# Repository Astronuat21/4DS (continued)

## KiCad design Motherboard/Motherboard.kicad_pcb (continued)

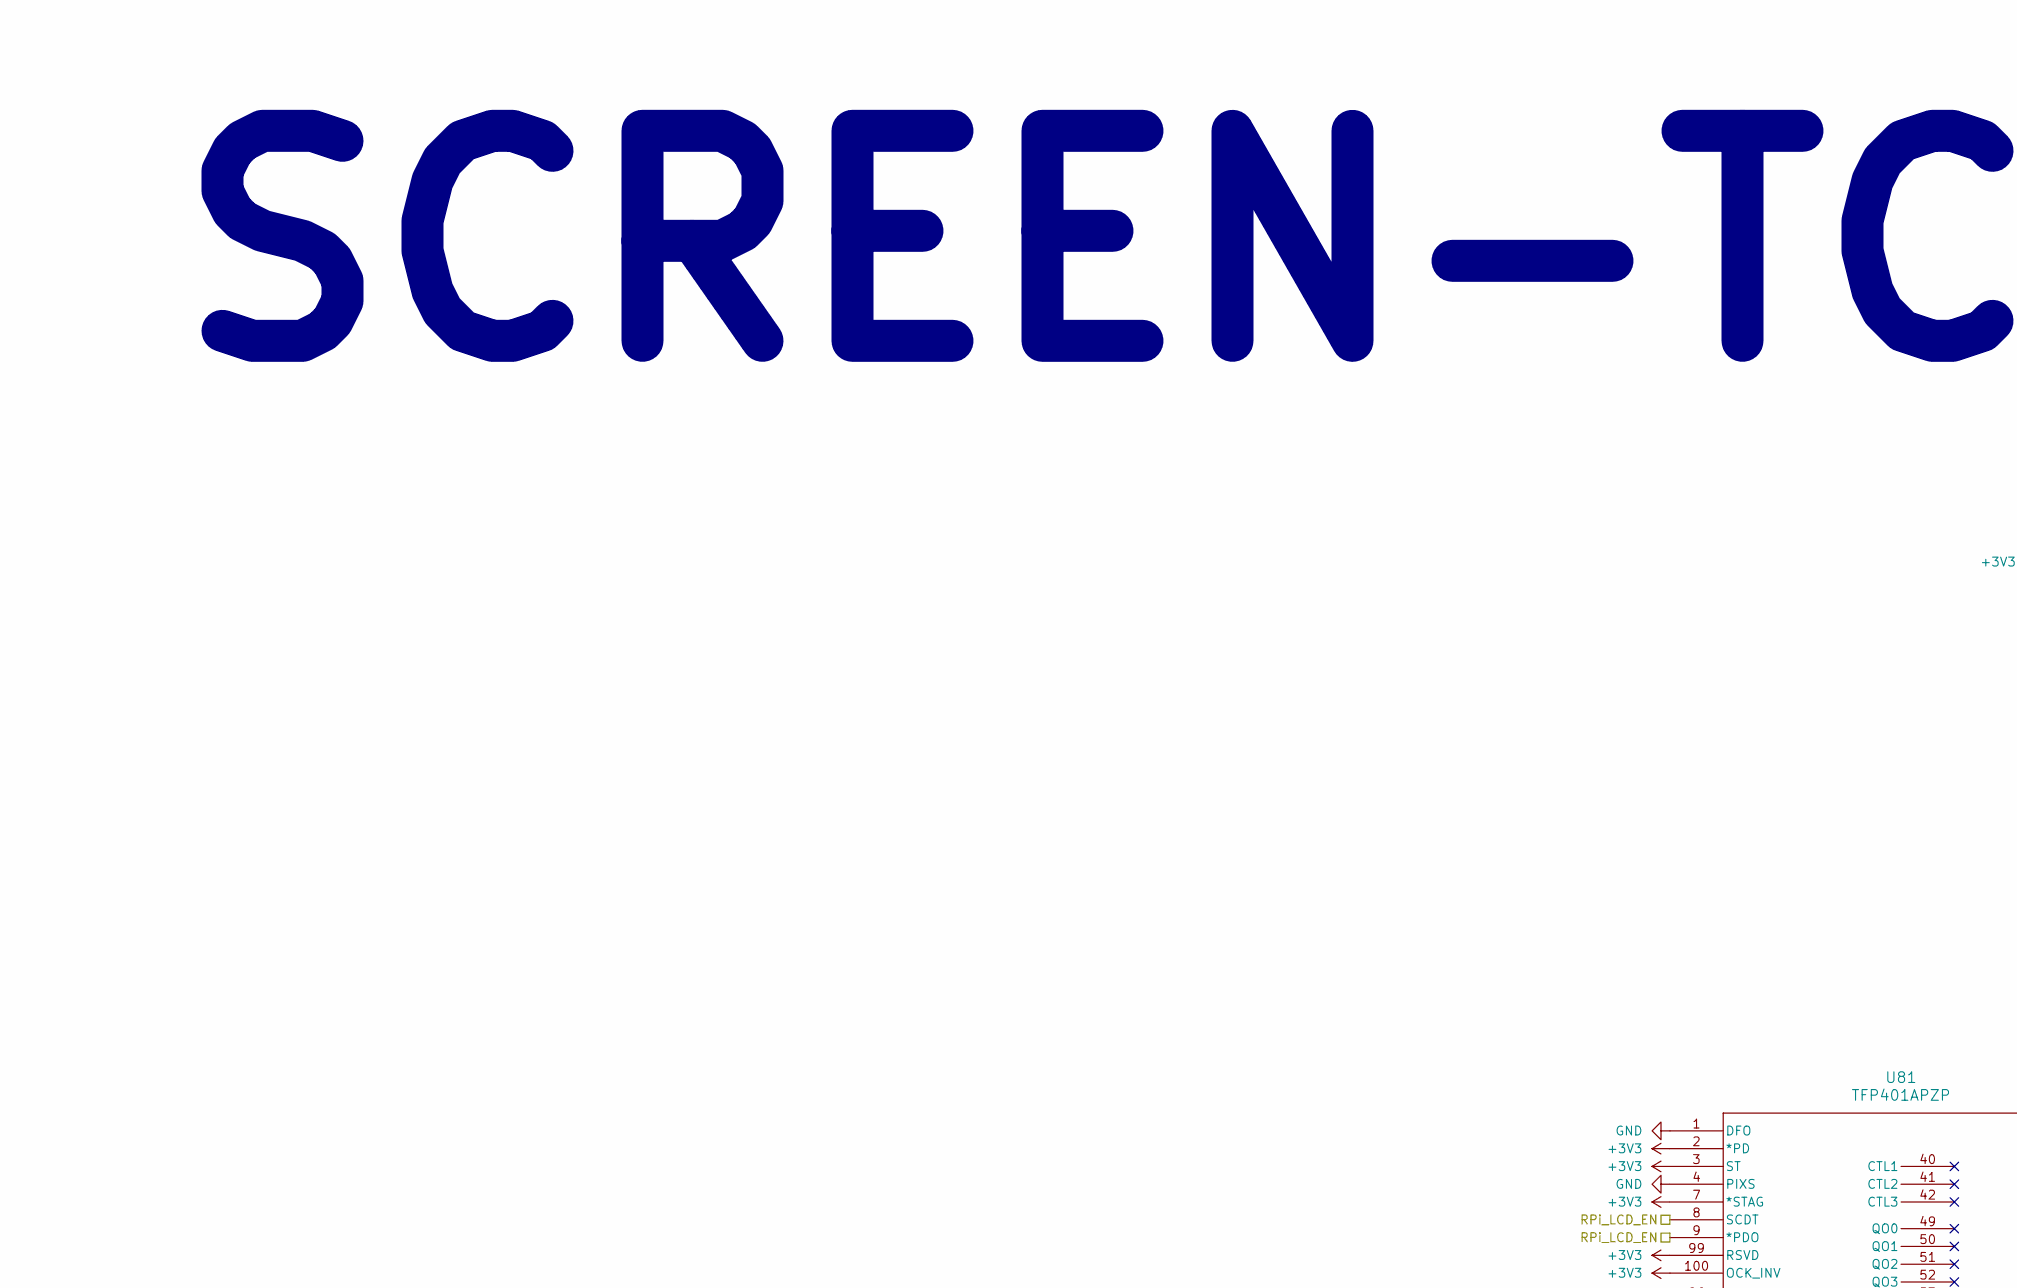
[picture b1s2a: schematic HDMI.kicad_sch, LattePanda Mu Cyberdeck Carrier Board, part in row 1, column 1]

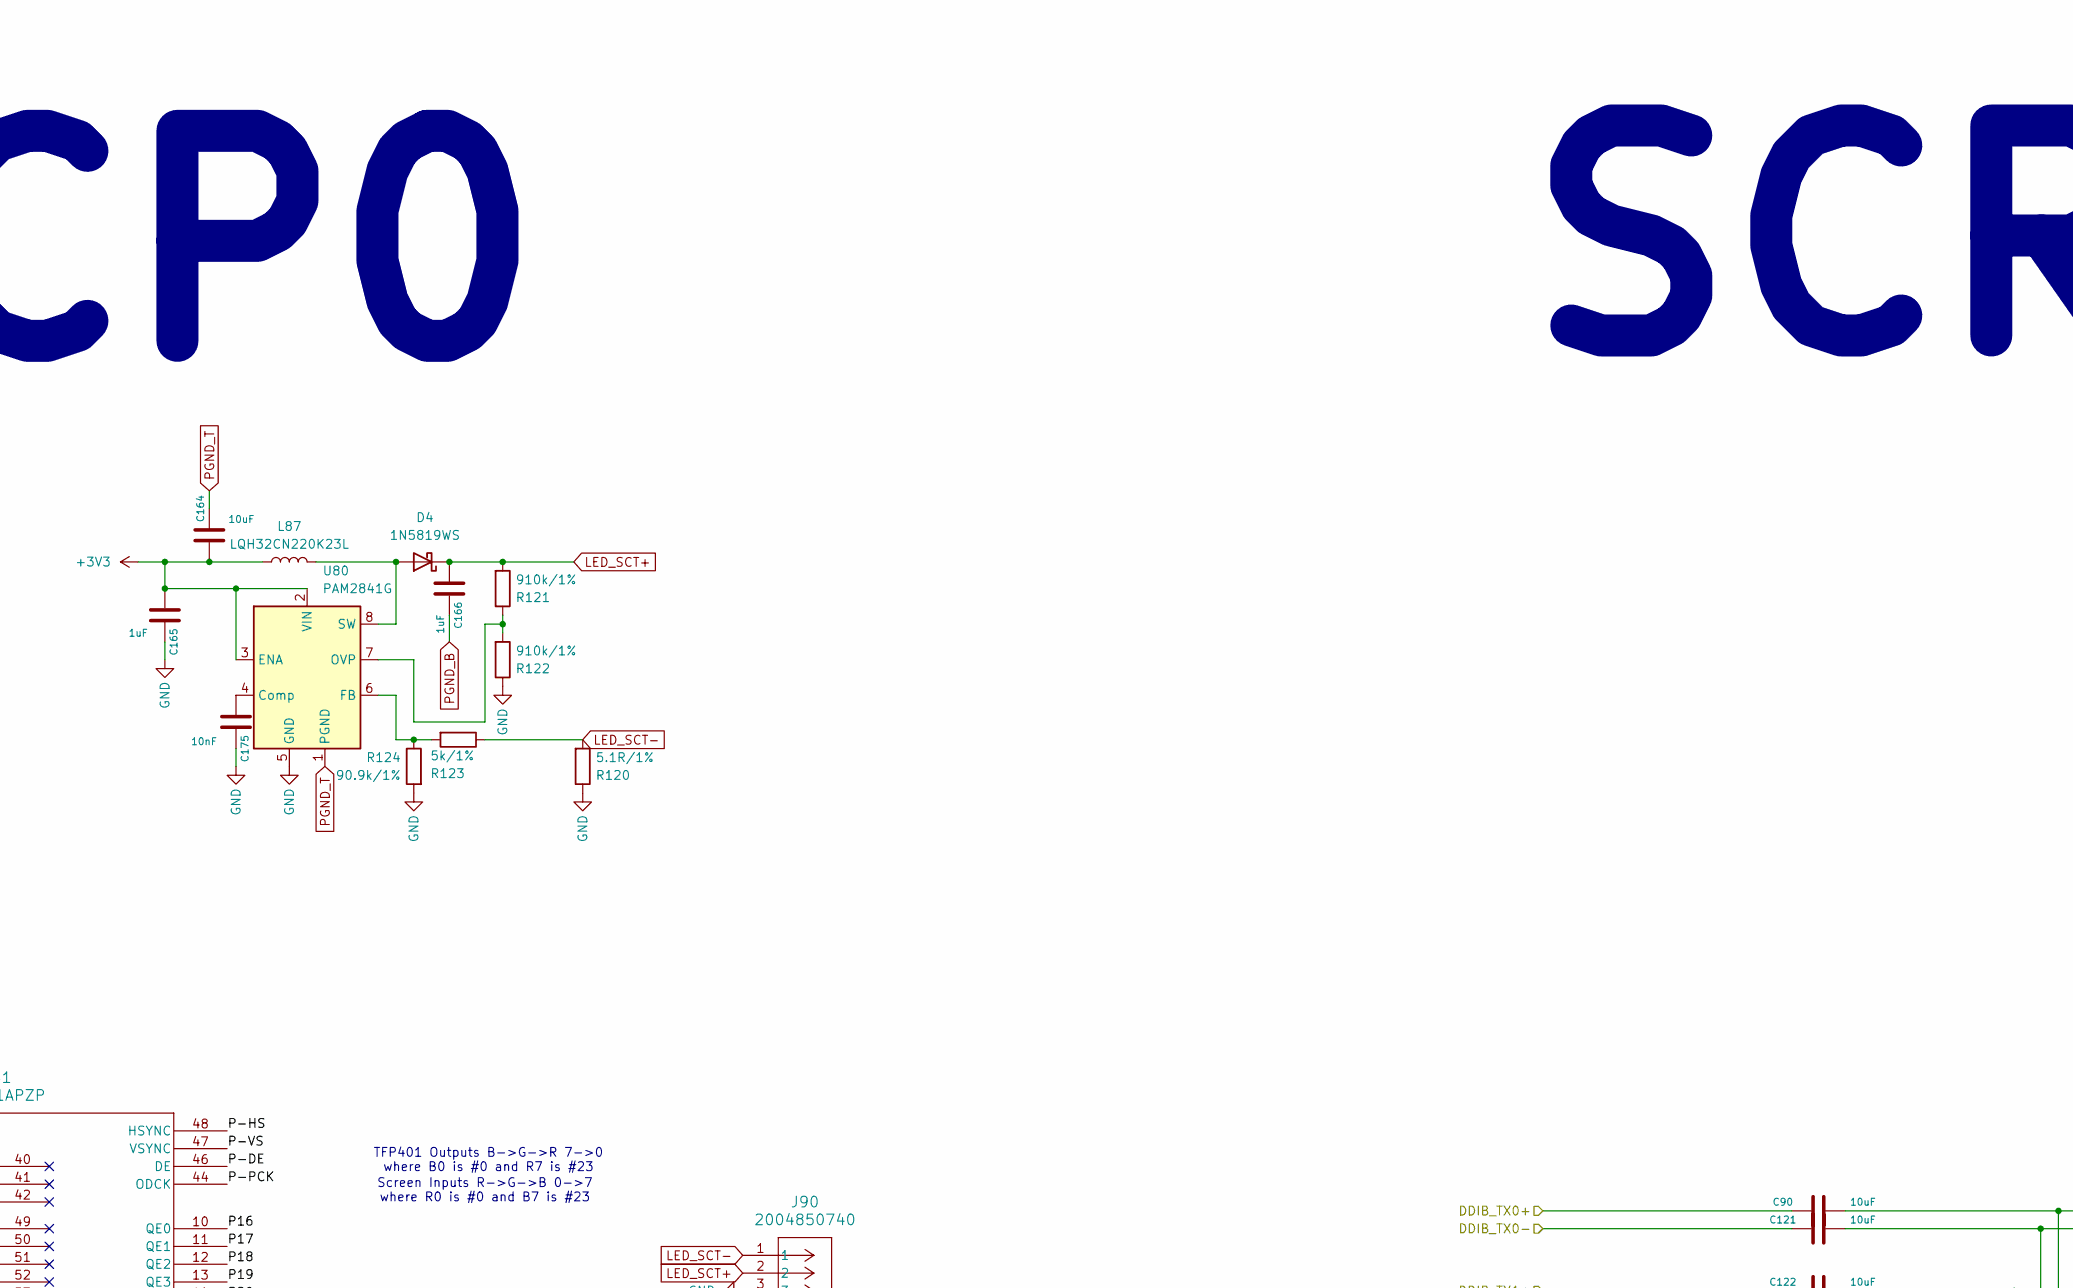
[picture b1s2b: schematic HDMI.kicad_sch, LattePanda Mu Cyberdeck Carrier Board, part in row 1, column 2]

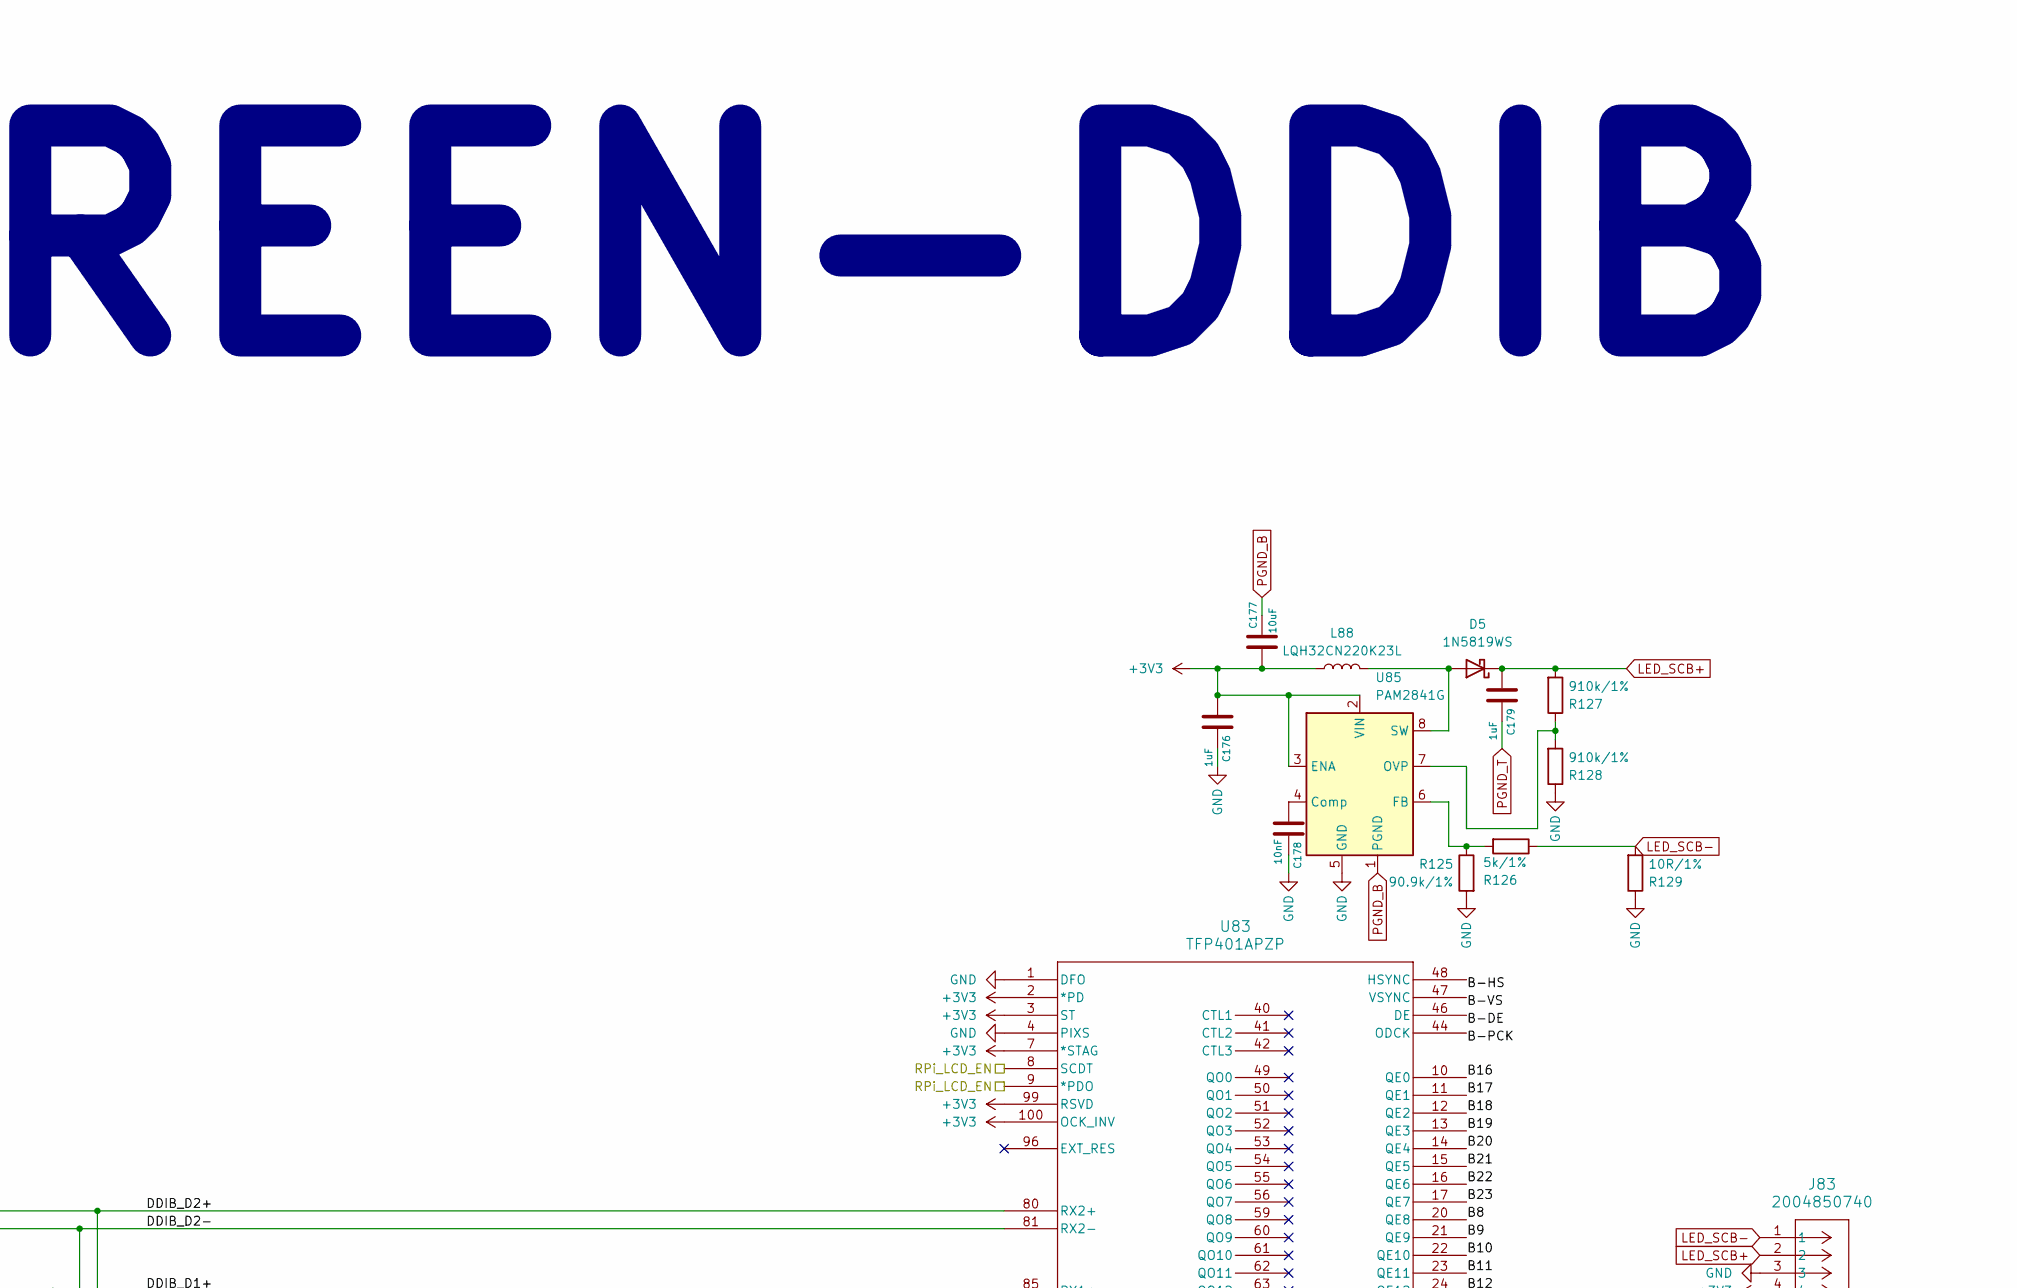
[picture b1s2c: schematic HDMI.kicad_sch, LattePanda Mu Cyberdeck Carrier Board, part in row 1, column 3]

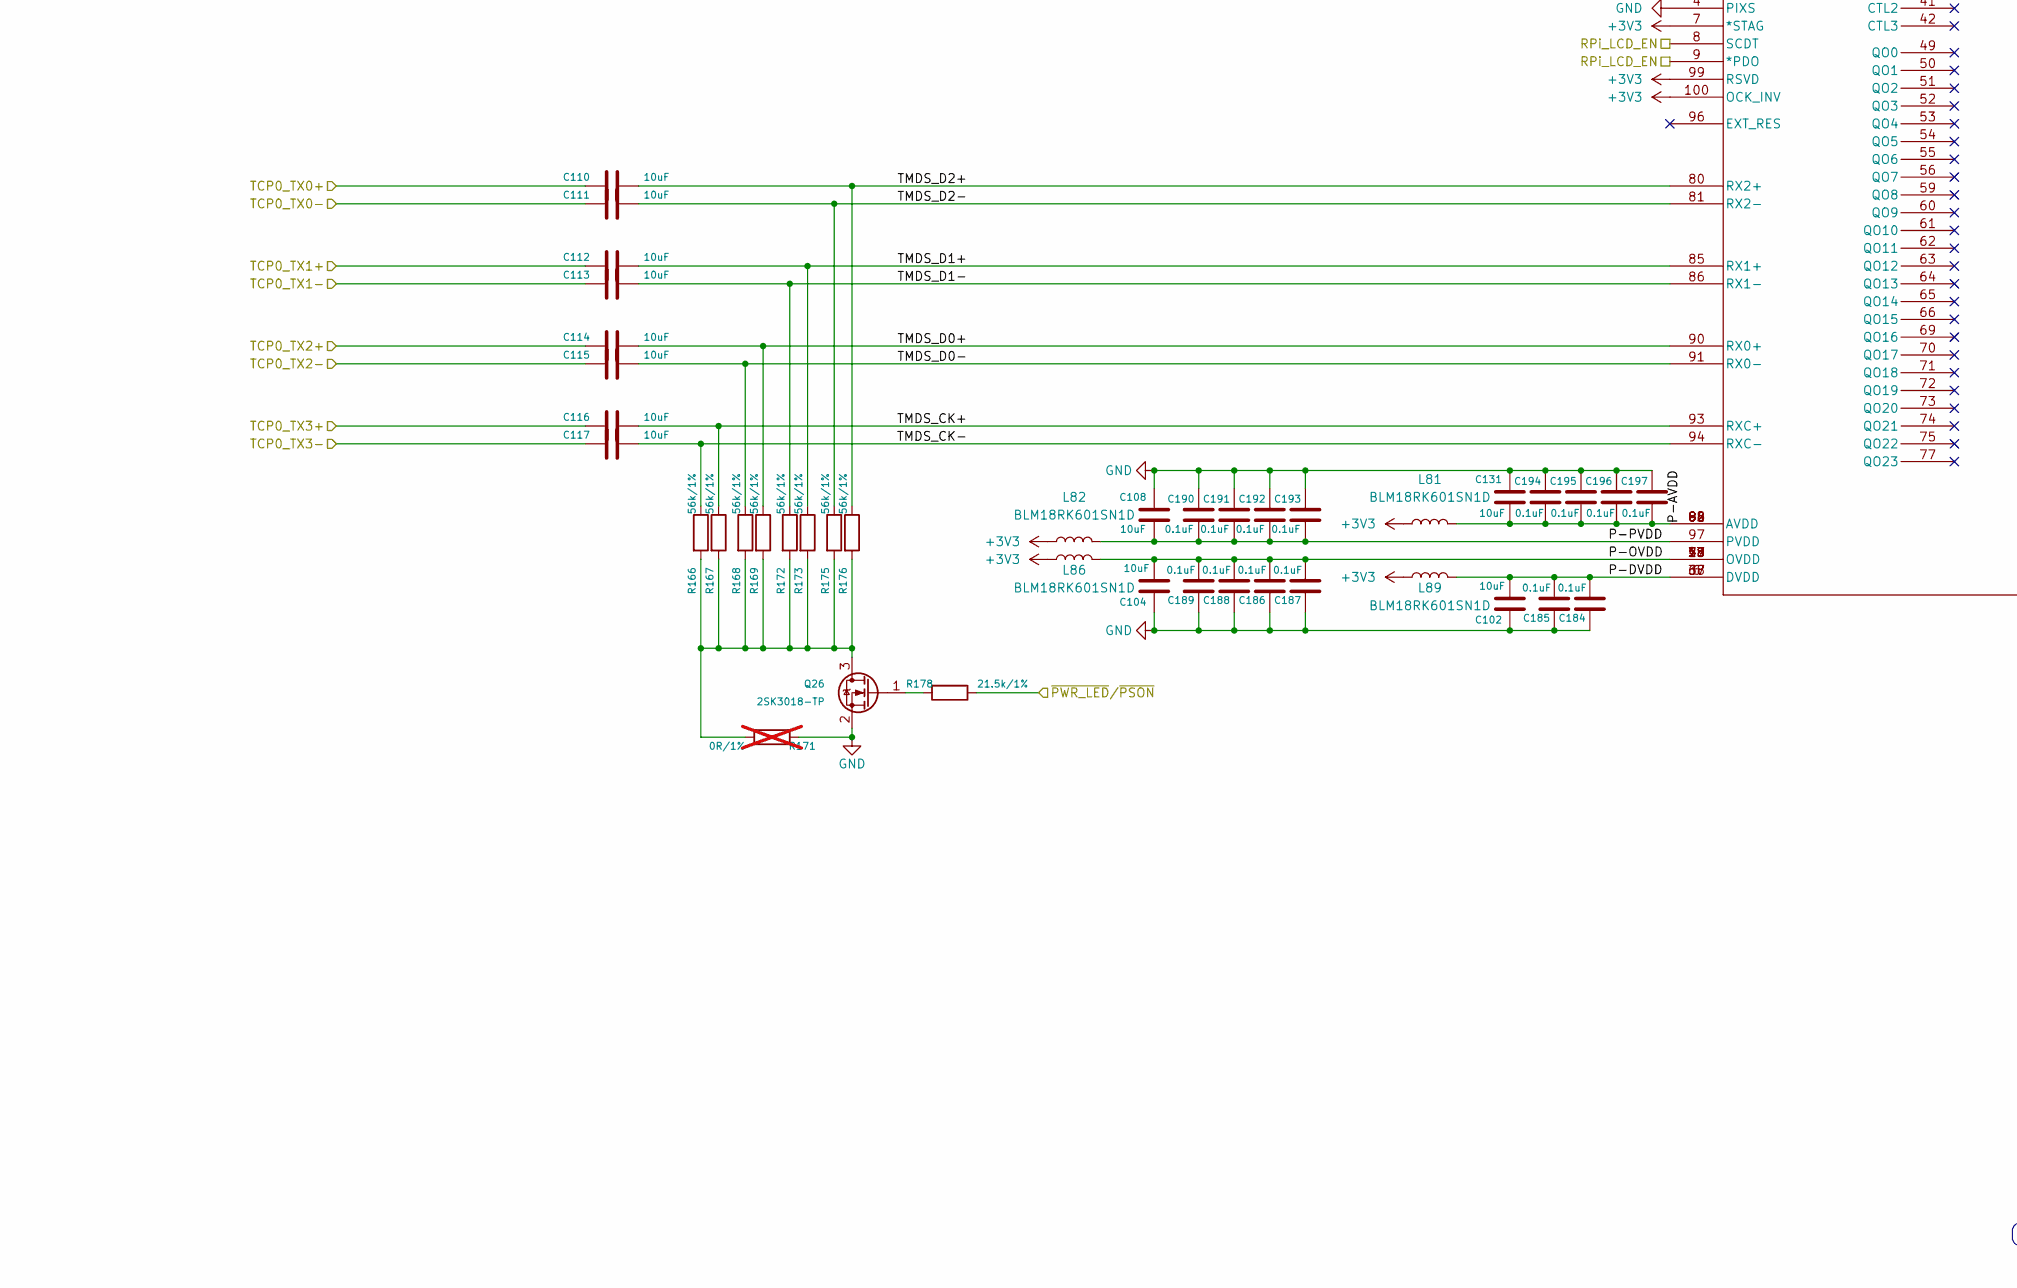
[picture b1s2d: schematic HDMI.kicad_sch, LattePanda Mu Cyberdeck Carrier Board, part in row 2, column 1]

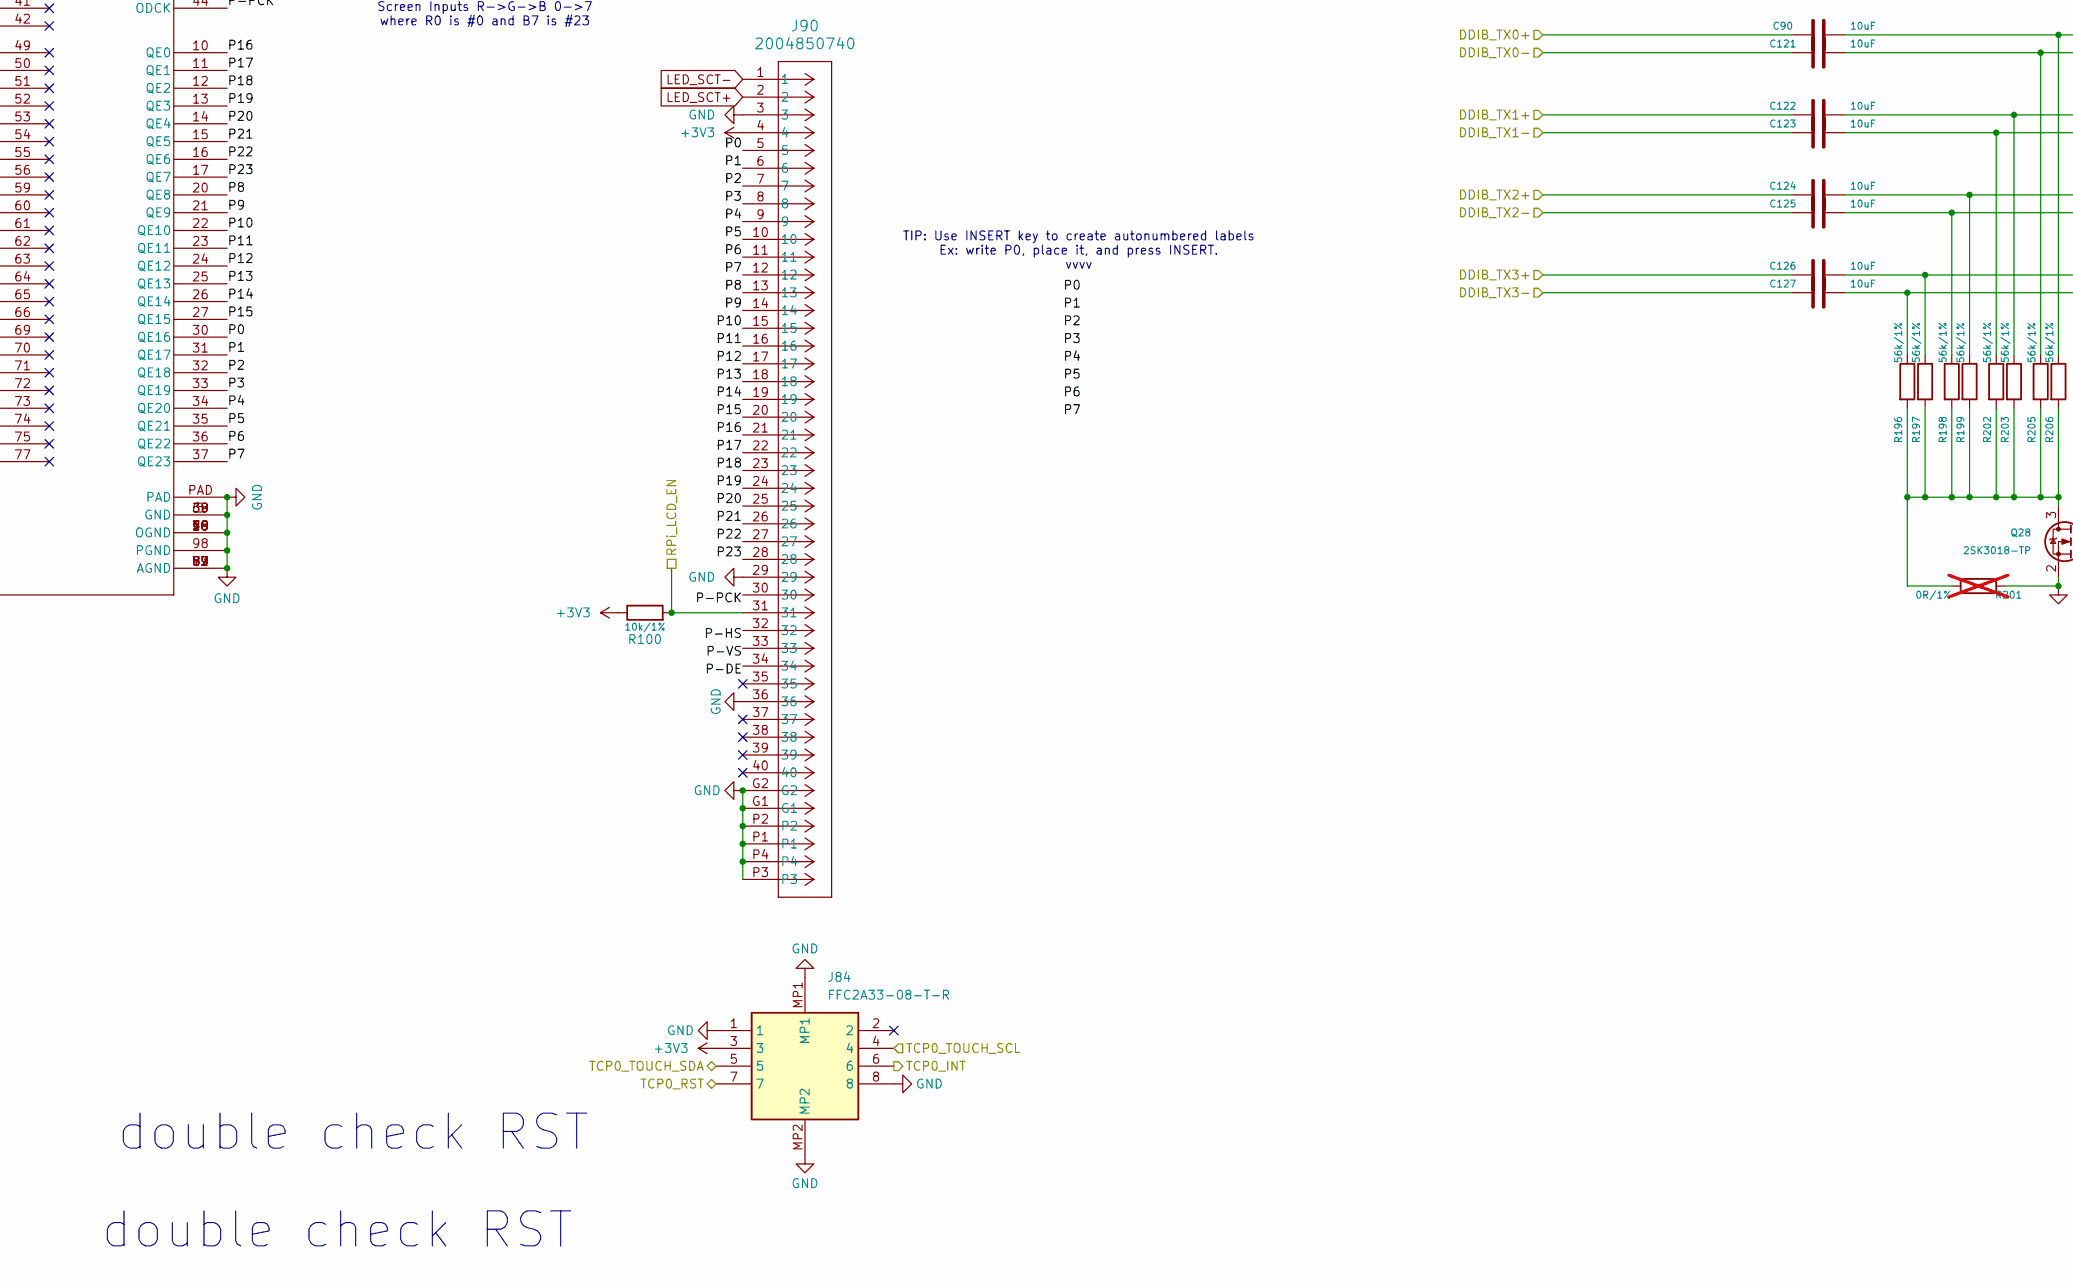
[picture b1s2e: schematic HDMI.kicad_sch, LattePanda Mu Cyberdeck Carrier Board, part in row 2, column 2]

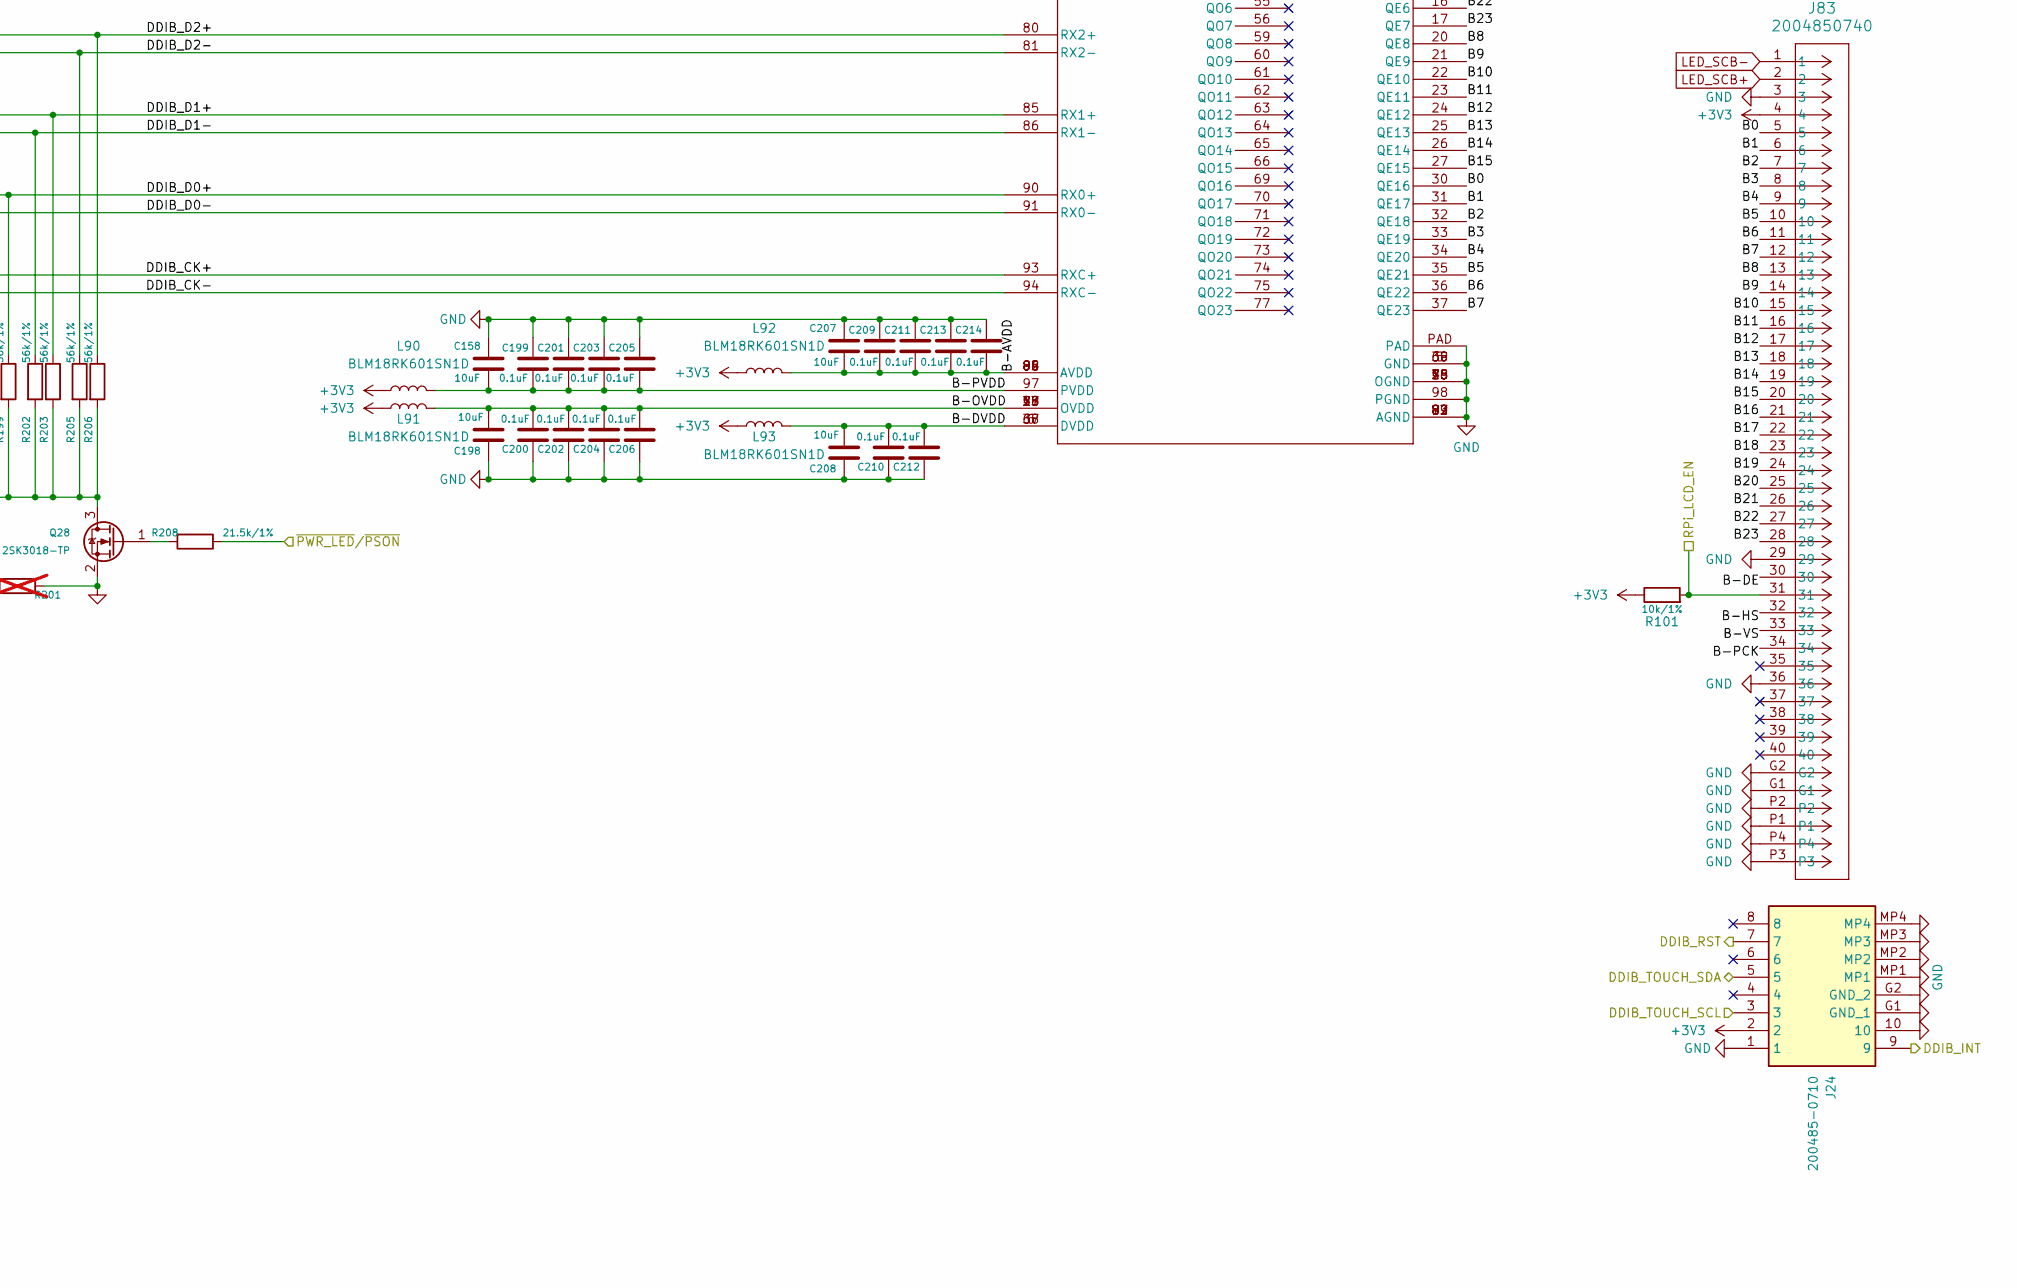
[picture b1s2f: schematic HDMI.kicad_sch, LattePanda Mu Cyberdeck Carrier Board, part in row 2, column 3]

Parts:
C90, C102, C104, C108, C110, C111, C112, C113, C114, C115, C116, C117, C121, C122, C123, C124, C125, C126, C127, C131, C164, C177, C207, C208: 10uF; C_0402_1005Metric; MPN GMC04X5R106M10NT
C158, C198: 10uF; C_0402_1005Metric; MPN GRM155R60J106ME15D
C165, C166, C176, C179: 1uF; C_0402_1005Metric; MPN TCC0402X5R105M100AT
C175, C178: 10nF; C_0402_1005Metric; MPN GRM155R61C103KA01D
C184, C185, C186, C187, C188, C189, C190, C191, C192, C193, C194, C195, C196, C197, C199, C200, C201, C202, C203, C204, C205, C206, C209, C210, C211, C212, C213, C214: 0.1uF; C_0402_1005Metric; MPN any/open
D4, D5: 1N5819WS; D_SOD-323; MPN 1N5819WS
J24: 200485-0710; 2004850710; MPN 2004850710
J83, J90: 2004850740; CON_2004850740; MPN 2004850740
J84: FFC2A33-08-T-R; FFC2A3308TR; MPN FFC2A33-08-T-R
L81, L82, L86, L89, L90, L91, L92, L93: BLM18RK601SN1D; L_0603_1608Metric; MPN BLM18RK601SN1D
L87, L88: LQH32CN220K23L; LQH32DN100K23L; MPN LQH32CN220K23L
Q26, Q28: 2SK3018-TP; SOT-89-3; MPN 2SK3018-TP
R100, R101: 10k/1%; R_0402_1005Metric; MPN MCR01MZPF1002
R120: 5.1R/1%; R_0402_1005Metric; MPN AC0402FR-075R1L
R121, R122, R127, R128: 910k/1%; R_0402_1005Metric; MPN 0402WGF9103TCE
R123, R126: 5k/1%; R_0402_1005Metric; MPN RC0402FR-075KL
R124, R125: 90.9k/1%; R_0805_2012Metric; MPN any/open
R129: 10R/1%; R_0402_1005Metric; MPN CRG0402F10R
R166, R167, R168, R169, R172, R173, R175, R176, R196, R197, R198, R199, R202, R203, R205, R206: 56k/1%; R_0402_1005Metric; MPN CRGCQ0402F56K
R171, R201: 0R/1%; R_0402_1005Metric; not fitted
R178, R208: 21.5k/1%; R_0402_1005Metric; MPN 0402WGF2152TCE
U80, U85: PAM2841G; DFN-8-1EP_2x2mm_P0.5mm_EP0.86x1.55mm; MPN PAM2841GR
U81, U83: TFP401APZP; PZP100_5P2X5P2; MPN TFP401APZP

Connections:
+3V3: C164.2, C165.2, C176.2, C177.2, J24.2, J83.4, J84.3, J90.4, L81.1, L82.1, L86.1, L87.1, L87.3, L88.1, L88.3, L89.1, L90.1, L91.1, L92.1, L93.1, R100.1, R101.1, U80.2 (VIN), U80.3 (ENA), U81.2 (*PD), U81.3 (ST), U81.7 (*STAG), U81.99 (RSVD), U81.100 (OCK_INV), U83.2 (*PD), U83.3 (ST), U83.7 (*STAG), U83.99 (RSVD), U83.100 (OCK_INV), U85.2 (VIN), U85.3 (ENA); also elsewhere on the board
/LattePanda Module/DDIB_INT: J24.9; also elsewhere on the board
/LattePanda Module/DDIB_RST: J24.7; also elsewhere on the board
/LattePanda Module/DDIB_TOUCH_SCL: J24.3; also elsewhere on the board
/LattePanda Module/DDIB_TOUCH_SDA: J24.5; also elsewhere on the board
/LattePanda Module/DDIB_TX0+: C90.1; also elsewhere on the board
/LattePanda Module/DDIB_TX0-: C121.1; also elsewhere on the board
/LattePanda Module/DDIB_TX1+: C122.1; also elsewhere on the board
/LattePanda Module/DDIB_TX1-: C123.1; also elsewhere on the board
/LattePanda Module/DDIB_TX2+: C124.1; also elsewhere on the board
/LattePanda Module/DDIB_TX2-: C125.1; also elsewhere on the board
/LattePanda Module/DDIB_TX3+: C126.1; also elsewhere on the board
/LattePanda Module/DDIB_TX3-: C127.1; also elsewhere on the board
/LattePanda Module/RPi_LCD_EN: J83.31, J90.31, R100.2, R101.2, U81.8 (SCDT), U81.9 (*PDO), U83.8 (SCDT), U83.9 (*PDO); also elsewhere on the board
/LattePanda Module/TCP0_INT: J84.6; also elsewhere on the board
/LattePanda Module/TCP0_RST: J84.7; also elsewhere on the board
/LattePanda Module/TCP0_TOUCH_SCL: J84.4; also elsewhere on the board
/LattePanda Module/TCP0_TOUCH_SDA: J84.5; also elsewhere on the board
/LattePanda Module/TCP0_TX0+: C110.1; also elsewhere on the board
/LattePanda Module/TCP0_TX0-: C111.1; also elsewhere on the board
/LattePanda Module/TCP0_TX1+: C112.1; also elsewhere on the board
/LattePanda Module/TCP0_TX1-: C113.1; also elsewhere on the board
/LattePanda Module/TCP0_TX2+: C114.1; also elsewhere on the board
/LattePanda Module/TCP0_TX2-: C115.1; also elsewhere on the board
/LattePanda Module/TCP0_TX3+: C116.1; also elsewhere on the board
/LattePanda Module/TCP0_TX3-: C117.1; also elsewhere on the board
/RGB/B0: J83.5, U83.30 (QE16)
/RGB/B1: J83.6, U83.31 (QE17)
/RGB/B2: J83.7, U83.32 (QE18)
/RGB/B3: J83.8, U83.33 (QE19)
/RGB/B4: J83.9, U83.34 (QE20)
/RGB/B5: J83.10, U83.35 (QE21)
/RGB/B6: J83.11, U83.36 (QE22)
/RGB/B7: J83.12, U83.37 (QE23)
/RGB/B8: J83.13, U83.20 (QE8)
/RGB/B9: J83.14, U83.21 (QE9)
/RGB/B10: J83.15, U83.22 (QE10)
/RGB/B11: J83.16, U83.23 (QE11)
/RGB/B12: J83.17, U83.24 (QE12)
/RGB/B13: J83.18, U83.25 (QE13)
/RGB/B14: J83.19, U83.26 (QE14)
/RGB/B15: J83.20, U83.27 (QE15)
/RGB/B16: J83.21, U83.10 (QE0)
/RGB/B17: J83.22, U83.11 (QE1)
/RGB/B18: J83.23, U83.12 (QE2)
/RGB/B19: J83.24, U83.13 (QE3)
/RGB/B20: J83.25, U83.14 (QE4)
/RGB/B21: J83.26, U83.15 (QE5)
/RGB/B22: J83.27, U83.16 (QE6)
/RGB/B23: J83.28, U83.17 (QE7)
/RGB/B-AVDD: C207.2, C209.1, C211.1, C213.1, C214.1, L92.2, U83.82 (AVDD), U83.84 (AVDD), U83.88 (AVDD), U83.95 (AVDD)
/RGB/B-DE: J83.30, U83.46 (DE)
/RGB/B-DVDD: C208.2, C210.1, C212.1, L93.2, U83.6 (DVDD), U83.38 (DVDD), U83.67 (DVDD)
/RGB/B-HS: J83.32, U83.48 (HSYNC)
/RGB/B-OVDD: C198.2, C200.1, C202.1, C204.1, C206.1, L91.2, U83.18 (OVDD), U83.29 (OVDD), U83.43 (OVDD), U83.57 (OVDD), U83.78 (OVDD)
/RGB/B-PCK: J83.34, U83.44 (ODCK)
/RGB/B-PVDD: C158.2, C199.1, C201.1, C203.1, C205.1, L90.2, U83.97 (PVDD)
/RGB/B-VS: J83.33, U83.47 (VSYNC)
/RGB/DDIB_CK+: C126.2, R197.1, U83.93 (RXC+)
/RGB/DDIB_CK-: C127.2, R196.1, U83.94 (RXC-)
/RGB/DDIB_D0+: C124.2, R199.1, U83.90 (RX0+)
/RGB/DDIB_D0-: C125.2, R198.1, U83.91 (RX0-)
/RGB/DDIB_D1+: C122.2, R203.1, U83.85 (RX1+)
/RGB/DDIB_D1-: C123.2, R202.1, U83.86 (RX1-)
/RGB/DDIB_D2+: C90.2, R206.1, U83.80 (RX2+)
/RGB/DDIB_D2-: C121.2, R205.1, U83.81 (RX2-)
/RGB/P0: J90.5, U81.30 (QE16)
/RGB/P1: J90.6, U81.31 (QE17)
/RGB/P2: J90.7, U81.32 (QE18)
/RGB/P3: J90.8, U81.33 (QE19)
/RGB/P4: J90.9, U81.34 (QE20)
/RGB/P5: J90.10, U81.35 (QE21)
/RGB/P6: J90.11, U81.36 (QE22)
/RGB/P7: J90.12, U81.37 (QE23)
/RGB/P8: J90.13, U81.20 (QE8)
/RGB/P9: J90.14, U81.21 (QE9)
/RGB/P10: J90.15, U81.22 (QE10)
/RGB/P11: J90.16, U81.23 (QE11)
/RGB/P12: J90.17, U81.24 (QE12)
/RGB/P13: J90.18, U81.25 (QE13)
/RGB/P14: J90.19, U81.26 (QE14)
/RGB/P15: J90.20, U81.27 (QE15)
/RGB/P16: J90.21, U81.10 (QE0)
/RGB/P17: J90.22, U81.11 (QE1)
/RGB/P18: J90.23, U81.12 (QE2)
/RGB/P19: J90.24, U81.13 (QE3)
/RGB/P20: J90.25, U81.14 (QE4)
/RGB/P21: J90.26, U81.15 (QE5)
/RGB/P22: J90.27, U81.16 (QE6)
/RGB/P23: J90.28, U81.17 (QE7)
/RGB/P-AVDD: C131.2, C194.1, C195.1, C196.1, C197.1, L81.2, U81.82 (AVDD), U81.84 (AVDD), U81.88 (AVDD), U81.95 (AVDD)
/RGB/P-DE: J90.34, U81.46 (DE)
/RGB/P-DVDD: C102.2, C184.1, C185.1, L89.2, U81.6 (DVDD), U81.38 (DVDD), U81.67 (DVDD)
/RGB/P-HS: J90.32, U81.48 (HSYNC)
/RGB/P-OVDD: C104.2, C186.1, C187.1, C188.1, C189.1, L86.2, U81.18 (OVDD), U81.29 (OVDD), U81.43 (OVDD), U81.57 (OVDD), U81.78 (OVDD)
/RGB/P-PCK: J90.30, U81.44 (ODCK)
/RGB/P-PVDD: C108.2, C190.1, C191.1, C192.1, C193.1, L82.2, U81.97 (PVDD)
/RGB/P-VS: J90.33, U81.47 (VSYNC)
/RGB/TMDS_CK+: C116.2, R167.1, U81.93 (RXC+)
/RGB/TMDS_CK-: C117.2, R166.1, U81.94 (RXC-)
/RGB/TMDS_D0+: C114.2, R169.1, U81.90 (RX0+)
/RGB/TMDS_D0-: C115.2, R168.1, U81.91 (RX0-)
/RGB/TMDS_D1+: C112.2, R173.1, U81.85 (RX1+)
/RGB/TMDS_D1-: C113.2, R172.1, U81.86 (RX1-)
/RGB/TMDS_D2+: C110.2, R176.1, U81.80 (RX2+)
/RGB/TMDS_D2-: C111.2, R175.1, U81.81 (RX2-)
/~PWR_LED/~PSON: R178.1, R208.1; also elsewhere on the board
GND: C102.1, C104.1, C108.1, C131.1, C158.1, C165.1, C175.1, C176.1, C178.1, C184.2, C185.2, C186.2, C187.2, C188.2, C189.2, C190.2, C191.2, C192.2, C193.2, C194.2, C195.2, C196.2, C197.2, C198.1, C199.2, C200.2, C201.2, C202.2, C203.2, C204.2, C205.2, C206.2, C207.1, C208.1, C209.2, C210.2, C211.2, C212.2, C213.2, C214.2, J24.1, J24.10, J24.G1 (GND_1), J24.G2 (GND_2), J24.MP1, J24.MP2, J24.MP3, J24.MP4, J83.3, J83.29, J83.36, J83.G1, J83.G2, J83.P1, J83.P2, J83.P3, J83.P4, J84.1, J84.8, J84.MP1, J84.MP2, J90.3, J90.29, J90.36, J90.G1, J90.G2, J90.P1, J90.P2, J90.P3, J90.P4, Q26.2 (S), Q28.2 (S), R120.1, R122.1, R124.2, R125.2, R128.1, R129.1, R171.2, R201.2, U80.5 (GND), U80.9 (GND), U81.1 (DFO), U81.4 (PIXS), U81.5 (GND), U81.19 (OGND), U81.28 (OGND), U81.39 (GND), U81.45 (OGND), U81.58 (OGND), U81.68 (GND), U81.76 (OGND), U81.79 (AGND), U81.83 (AGND), U81.87 (AGND), U81.89 (AGND), U81.92 (AGND), U81.98 (PGND), U81.PAD, U83.1 (DFO), U83.4 (PIXS), U83.5 (GND), U83.19 (OGND), U83.28 (OGND), U83.39 (GND), U83.45 (OGND), U83.58 (OGND), U83.68 (GND), U83.76 (OGND), U83.79 (AGND), U83.83 (AGND), U83.87 (AGND), U83.89 (AGND), U83.92 (AGND), U83.98 (PGND), U83.PAD, U85.5 (GND), U85.9 (GND); also elsewhere on the board
LED_SCB+: C179.2, D5.1 (K), J83.2, R127.2
LED_SCB-: J83.1, R126.1, R129.2
LED_SCT+: C166.2, D4.1 (K), J90.2, R121.2
LED_SCT-: J90.1, R120.2, R123.1
unnamed: D4.2 (A), L87.2, L87.4, U80.8 (SW)
unnamed: D5.2 (A), L88.2, L88.4, U85.8 (SW)
unnamed: Q26.3 (D), R166.2, R167.2, R168.2, R169.2, R171.1, R172.2, R173.2, R175.2, R176.2
unnamed: Q26.1 (G), R178.2
unnamed: Q28.3 (D), R196.2, R197.2, R198.2, R199.2, R201.1, R202.2, R203.2, R205.2, R206.2
unnamed: Q28.1 (G), R208.2
unnamed: C175.2, U80.4 (Comp)
unnamed: R123.2, R124.1, U80.6 (FB)
unnamed: R121.1, R122.2, U80.7 (OVP)
unnamed: C178.2, U85.4 (Comp)
unnamed: R125.1, R126.2, U85.6 (FB)
unnamed: R127.1, R128.2, U85.7 (OVP)
PGND_B: C166.1, C177.1, U85.1 (PGND)
PGND_T: C164.1, C179.1, U80.1 (PGND)

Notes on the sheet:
double check RST
TIP: Use INSERT key to create autonumbered labels Ex: write P0, place it, and press INSERT. vvvv
Screen Inputs R->G->B 0->7 where R0 is #0 and B7 is #23
TFP401 Outputs B->G->R 7->0 where B0 is #0 and R7 is #23
SCREEN-DDIB
SCREEN-TCP0
